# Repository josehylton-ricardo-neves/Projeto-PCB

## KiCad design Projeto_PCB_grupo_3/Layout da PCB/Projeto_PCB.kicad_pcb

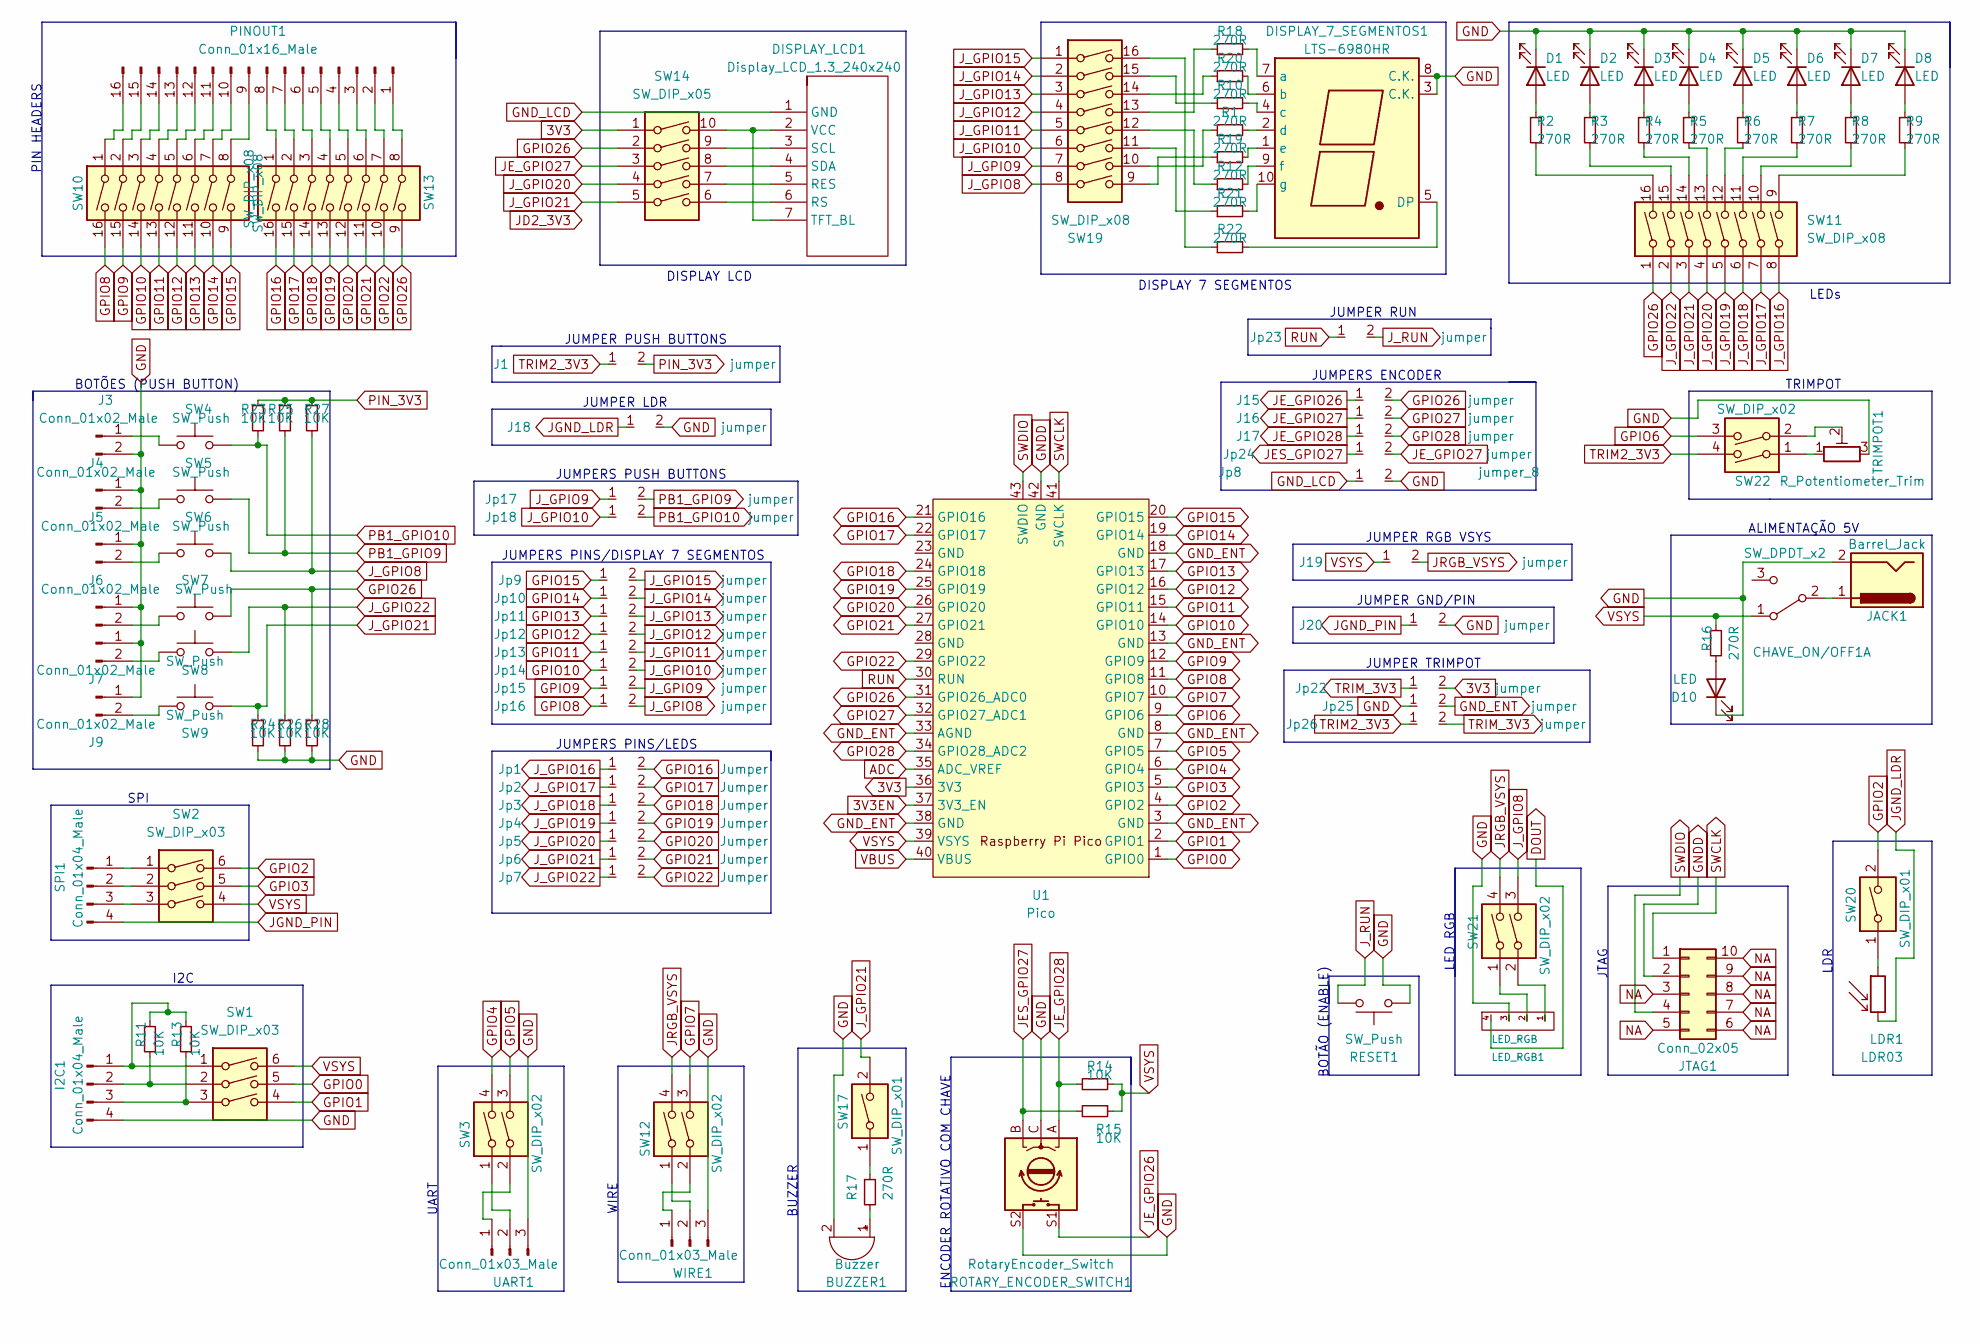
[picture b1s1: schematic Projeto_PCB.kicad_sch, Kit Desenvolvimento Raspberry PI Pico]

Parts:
BUZZER1: Buzzer; Buzzer_15x7.5RM7.6
CHAVE_ON/OFF1: SW_DPDT_x2; Chave 3 pin
D1, D2, D3, D4, D5, D6, D7, D8, D10: LED; LED_D3.0mm
DISPLAY_7_SEGMENTOS1: LTS-6980HR; 7SegmentLED_LTS6760_LTS6780
DISPLAY_LCD1: Display_LCD_1.3_240x240; Display IPS LCD 1.3″ 240×240
I2C1: Conn_01x04_Male; PinHeader_1x04_P2.54mm_Vertical
J1, J17: jumper; Jumper-Wire_12mm_Blue
J3, J4, J5, J6, J7, J9: Conn_01x02_Male; PinHeader_1x02_P2.54mm_Vertical
J15, J16, J18, J20: jumper; Jumper-Wire_20mm_Blue
J19: jumper; Jumper-Wire_30mm_Blue_correto
JACK1: Barrel_Jack; BarrelJack_CUI_PJ-063AH_Horizontal
JTAG1: Conn_02x05; PinHeader_2x05_P2.54mm_Vertical
Jp1, Jp2, Jp3, Jp4, Jp5, Jp6, Jp7: Jumper; Jumper-Wire_30mm_blue_adaptado
Jp8: jumper_8; Jumper-Wire_8mm_Blue
Jp9, Jp10, Jp11, Jp12, Jp13, Jp14, Jp15, Jp16, Jp23: jumper; Jumper-Wire_30mm_Blue_correto
Jp17, Jp18, Jp22, Jp24, Jp26: jumper; Jumper-Wire_8mm_Blue
Jp25: jumper; Jumper-Wire_12mm_Blue
LDR1: LDR03; R_LDR_10x8.5mm_P7.6mm_Vertical
LED_RGB1: LED_RGB
PINOUT1: Conn_01x16_Male; PinHeader_1x16_P2.54mm_Vertical
R1, R2, R3, R4, R5, R6, R7, R8, R9, R10, R12, R16, R17, R18, R19, R20, R21, R22: 270R; R_Axial_DIN0204_L3.6mm_D1.6mm_P5.08mm_Horizontal
R11, R13, R14, R15, R23, R24, R25, R26, R27, R28: 10K; R_Axial_DIN0204_L3.6mm_D1.6mm_P5.08mm_Horizontal
RESET1: SW_Push; SW_PUSH_6mm_H5mm
ROTARY_ENCODER_SWITCH1: RotaryEncoder_Switch; RotaryEncoder_Alps_EC11E-Switch_Vertical_H20mm
SPI1: Conn_01x04_Male; PinHeader_1x04_P2.54mm_Vertical
SW1, SW2: SW_DIP_x03; SW_DIP_SPSTx03_Slide_9.78x9.8mm_W7.62mm_P2.54mm
SW3, SW12, SW21, SW22: SW_DIP_x02; SW_DIP_SPSTx02_Slide_9.78x7.26mm_W7.62mm_P2.54mm
SW4, SW5, SW6, SW7, SW8, SW9: SW_Push; SW_PUSH_6mm_H5mm
SW10, SW11, SW13, SW19: SW_DIP_x08; SW_DIP_SPSTx08_Slide_9.78x22.5mm_W7.62mm_P2.54mm
SW14: SW_DIP_x05; SW_DIP_SPSTx05_Slide_9.78x14.88mm_W7.62mm_P2.54mm
SW17, SW20: SW_DIP_x01; SW_DIP_SPSTx01_Slide_9.78x4.72mm_W7.62mm_P2.54mm
TRIMPOT1: R_Potentiometer_Trim; Potentiometer_Bourns_3339H_Vertical
U1: Pico; RPi_Pico_TH
UART1: Conn_01x03_Male; PinHeader_1x03_P2.54mm_Vertical
WIRE1: Conn_01x03_Male; PinHeader_1x03_P2.54mm_Vertical

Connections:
3V3: Jp22.2, SW14.1, U1.36 (3V3)
3V3EN: U1.37 (3V3_EN)
ADC: U1.35 (ADC_VREF)
DOUT: LED_RGB1.4 (DOUT)
GND: BUZZER1.2 (+), D1.1 (K), D2.1 (K), D3.1 (K), D4.1 (K), D5.1 (K), D6.1 (K), D7.1 (K), D8.1 (K), D10.1 (K), DISPLAY_7_SEGMENTOS1.3 (C.K.), DISPLAY_7_SEGMENTOS1.8 (C.K.), I2C1.4, J3.2, J4.1, J5.1, J6.1, J7.1, J9.1, J18.2, J20.2, JACK1.2, Jp8.2, Jp25.1, LED_RGB1.3 (GND), R24.2, R26.2, R28.2, RESET1.1, ROTARY_ENCODER_SWITCH1.C, ROTARY_ENCODER_SWITCH1.S2, TRIMPOT1.3, UART1.3, WIRE1.3
GNDD: JTAG1.2, U1.42 (GND)
GND_ENT: Jp25.2, U1.3 (GND), U1.8 (GND), U1.13 (GND), U1.18 (GND), U1.33 (AGND), U1.38 (GND)
GND_LCD: DISPLAY_LCD1.1 (GND), Jp8.1
GPIO0: SW1.5, U1.1 (GPIO0)
GPIO1: SW1.4, U1.2 (GPIO1)
GPIO2: SW2.6, SW20.2, U1.4 (GPIO2)
GPIO3: SW2.5, U1.5 (GPIO3)
GPIO4: SW3.4, U1.6 (GPIO4)
GPIO5: SW3.3, U1.7 (GPIO5)
GPIO6: SW22.3, U1.9 (GPIO6)
GPIO7: SW12.3, U1.10 (GPIO7)
GPIO8: Jp16.1, SW10.16, U1.11 (GPIO8)
GPIO9: Jp15.1, SW10.15, U1.12 (GPIO9)
GPIO10: Jp14.1, SW10.14, U1.14 (GPIO10)
GPIO11: Jp13.1, SW10.13, U1.15 (GPIO11)
GPIO12: Jp12.1, SW10.12, U1.16 (GPIO12)
GPIO13: Jp11.1, SW10.11, U1.17 (GPIO13)
GPIO14: Jp10.1, SW10.10, U1.19 (GPIO14)
GPIO15: Jp9.1, SW10.9, U1.20 (GPIO15)
GPIO16: Jp1.2, SW13.16, U1.21 (GPIO16)
GPIO17: Jp2.2, SW13.15, U1.22 (GPIO17)
GPIO18: Jp3.2, SW13.14, U1.24 (GPIO18)
GPIO19: Jp4.2, SW13.13, U1.25 (GPIO19)
GPIO20: Jp5.2, SW13.12, U1.26 (GPIO20)
GPIO21: Jp6.2, SW13.11, U1.27 (GPIO21)
GPIO22: Jp7.2, SW13.10, U1.29 (GPIO22)
GPIO26: J15.2, R28.1, SW7.2, SW11.1, SW13.9, SW14.2, U1.31 (GPIO26_ADC0)
GPIO27: J16.2, U1.32 (GPIO27_ADC1)
GPIO28: J17.2, U1.34 (GPIO28_ADC2)
JES_GPIO27: Jp24.1, R15.2, ROTARY_ENCODER_SWITCH1.B
JE_GPIO26: J15.1, ROTARY_ENCODER_SWITCH1.S1
JE_GPIO27: J16.1, Jp24.2, SW14.3
JE_GPIO28: J17.1, R14.2, ROTARY_ENCODER_SWITCH1.A
JGND_LDR: J18.1, LDR1.2
JGND_PIN: J20.1, SPI1.4
JRGB_VSYS: J19.2, SW12.4, SW21.4
J_GPIO8: Jp16.2, R27.2, SW6.2, SW19.8, SW21.3
J_GPIO9: Jp15.2, Jp17.1, SW19.7
J_GPIO10: Jp14.2, Jp18.1, SW19.6
J_GPIO11: Jp13.2, SW19.5
J_GPIO12: Jp12.2, SW19.4
J_GPIO13: Jp11.2, SW19.3
J_GPIO14: Jp10.2, SW19.2
J_GPIO15: Jp9.2, SW19.1
J_GPIO16: Jp1.1, SW11.8
J_GPIO17: Jp2.1, SW11.7
J_GPIO18: Jp3.1, SW11.6
J_GPIO19: Jp4.1, SW11.5
J_GPIO20: Jp5.1, SW11.4, SW14.4
J_GPIO21: Jp6.1, R24.1, SW9.2, SW11.3, SW14.5, SW17.2
J_GPIO22: Jp7.1, R26.1, SW8.2, SW11.2
J_RUN: Jp23.2, RESET1.2
NA: JTAG1.3, JTAG1.5, JTAG1.6, JTAG1.7, JTAG1.8, JTAG1.9, JTAG1.10
unnamed: BUZZER1.1 (-), R17.2
unnamed: CHAVE_ON/OFF1.2 (B), JACK1.1
unnamed: D1.2 (A), R2.1
unnamed: D2.2 (A), R3.1
unnamed: D3.2 (A), R4.1
unnamed: D4.2 (A), R5.1
unnamed: D5.2 (A), R6.1
unnamed: D6.2 (A), R7.1
unnamed: D7.2 (A), R8.1
unnamed: D8.2 (A), R9.1
unnamed: D10.2 (A), R16.2
unnamed: DISPLAY_7_SEGMENTOS1.1 (e), R19.2
unnamed: DISPLAY_7_SEGMENTOS1.2 (d), R1.2
unnamed: DISPLAY_7_SEGMENTOS1.4 (c), R10.2
unnamed: DISPLAY_7_SEGMENTOS1.5 (DP), R22.2
unnamed: DISPLAY_7_SEGMENTOS1.6 (b), R20.2
unnamed: DISPLAY_7_SEGMENTOS1.7 (a), R18.2
unnamed: DISPLAY_7_SEGMENTOS1.9 (f), R12.2
unnamed: DISPLAY_7_SEGMENTOS1.10 (g), R21.2
unnamed: DISPLAY_LCD1.2 (VCC), DISPLAY_LCD1.7 (TFT_BL), SW14.10
unnamed: DISPLAY_LCD1.3 (SCL), SW14.9
unnamed: DISPLAY_LCD1.4 (SDA), SW14.8
unnamed: DISPLAY_LCD1.5 (RES), SW14.7
unnamed: DISPLAY_LCD1.6 (RS), SW14.6
unnamed: I2C1.1, R11.1, R13.1, SW1.1
unnamed: I2C1.2, R11.2, SW1.2
unnamed: I2C1.3, R13.2, SW1.3
unnamed: J3.1, SW4.1
unnamed: J4.2, SW5.1
unnamed: J5.2, SW6.1
unnamed: J6.2, SW7.1
unnamed: J7.2, SW8.1
unnamed: J9.2, SW9.1
unnamed: LDR1.1, SW20.1
unnamed: LED_RGB1.1 (DIN), SW21.2
unnamed: LED_RGB1.2 (VDD), SW21.1
unnamed: PINOUT1.1, SW13.8
unnamed: PINOUT1.2, SW13.7
unnamed: PINOUT1.3, SW13.6
unnamed: PINOUT1.4, SW13.5
unnamed: PINOUT1.5, SW13.4
unnamed: PINOUT1.6, SW13.3
unnamed: PINOUT1.7, SW13.2
unnamed: PINOUT1.8, SW13.1
unnamed: PINOUT1.9, SW10.8
unnamed: PINOUT1.10, SW10.7
unnamed: PINOUT1.11, SW10.6
unnamed: PINOUT1.12, SW10.5
unnamed: PINOUT1.13, SW10.4
unnamed: PINOUT1.14, SW10.3
unnamed: PINOUT1.15, SW10.2
unnamed: PINOUT1.16, SW10.1
unnamed: R2.2, SW11.16
unnamed: R4.2, SW11.14
unnamed: R5.2, SW11.13
unnamed: R6.2, SW11.12
unnamed: R7.2, SW11.11
unnamed: R9.2, SW11.9
unnamed: R17.1, SW17.1
unnamed: SPI1.1, SW2.1
unnamed: SPI1.2, SW2.2
unnamed: SPI1.3, SW2.3
unnamed: SW3.1, UART1.2
unnamed: SW3.2, UART1.1
unnamed: R8.2, SW11.10
unnamed: R3.2, SW11.15
unnamed: SW12.1, WIRE1.2
unnamed: SW12.2, WIRE1.1
unnamed: R19.1, SW19.9
unnamed: R1.1, SW19.10
unnamed: R21.1, SW19.11
unnamed: R12.1, SW19.12
unnamed: R18.1, SW19.13
unnamed: R20.1, SW19.14
unnamed: R10.1, SW19.15
unnamed: R22.1, SW19.16
unnamed: SW22.1, TRIMPOT1.1
unnamed: SW22.2, TRIMPOT1.2
PB1_GPIO9: Jp17.2, R25.2, SW5.2
PB1_GPIO10: Jp18.2, R23.2, SW4.2
PIN_3V3: J1.2, R23.1, R25.1, R27.1
RUN: Jp23.1, U1.30 (RUN)
SWCLK: JTAG1.1, U1.41 (SWCLK)
SWDIO: JTAG1.4, U1.43 (SWDIO)
TRIM2_3V3: J1.1, Jp26.1, SW22.4
TRIM_3V3: Jp22.1, Jp26.2
VBUS: U1.40 (VBUS)
VSYS: CHAVE_ON/OFF1.1 (A), J19.1, R14.1, R15.1, R16.1, SW1.6, SW2.4, U1.39 (VSYS)

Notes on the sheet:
BOTÃO (ENABLE)
JUMPER LDR
JUMPER GND/PIN
JUMPER PUSH BUTTONS
BOTÕES (PUSH BUTTON)
PIN HEADERS
LED RGB
LEDs
WIRE
JUMPER TRIMPOT
JUMPERS PUSH BUTTONS
DISPLAY LCD
LDR
BUZZER
JUMPER RGB VSYS
SPI
I2C
JUMPERS PINS/LEDS
JUMPERS ENCODER
DISPLAY 7 SEGMENTOS
ALIMENTAÇÃO 5V
UART
JUMPERS PINS/DISPLAY 7 SEGMENTOS
JTAG
JUMPER RUN
TRIMPOT
ENCODER ROTATIVO COM CHAVE

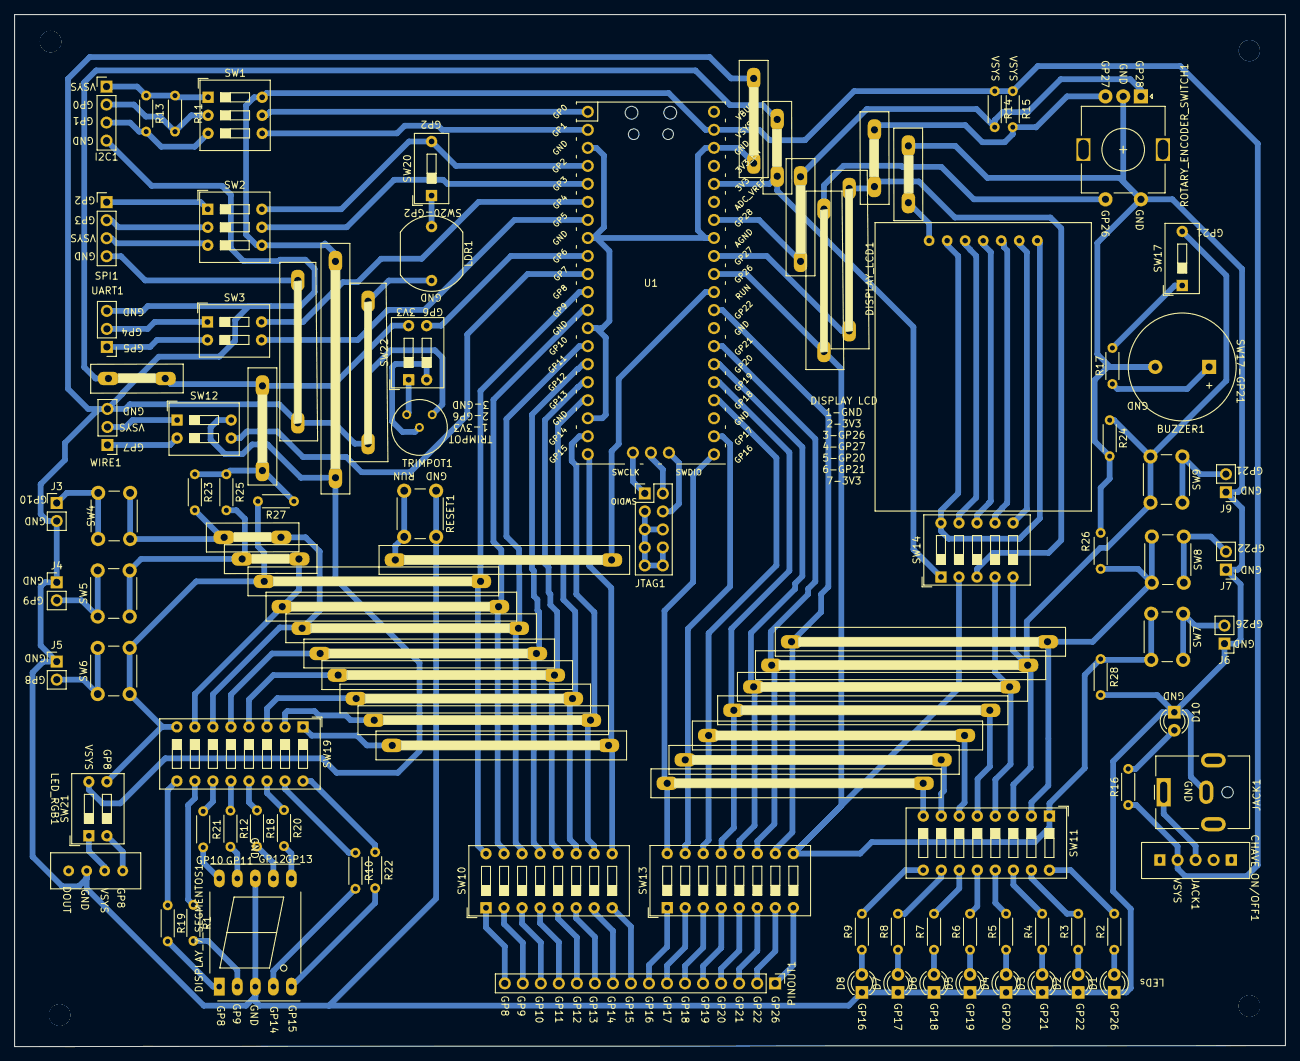
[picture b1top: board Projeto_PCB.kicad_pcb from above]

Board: 2 copper layers, 179.1 x 145.4 mm, 109 parts (0 on the bottom side), 142 nets.

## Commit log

2022-06-04 kit PCB raspberry pi pico.
